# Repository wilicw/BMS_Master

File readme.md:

# BMS Master board PCB
NCKU Formula racing 2025
BMS Master using TI's BQ79600-Q1 as communication module and STM32F103C8T6 as MCU

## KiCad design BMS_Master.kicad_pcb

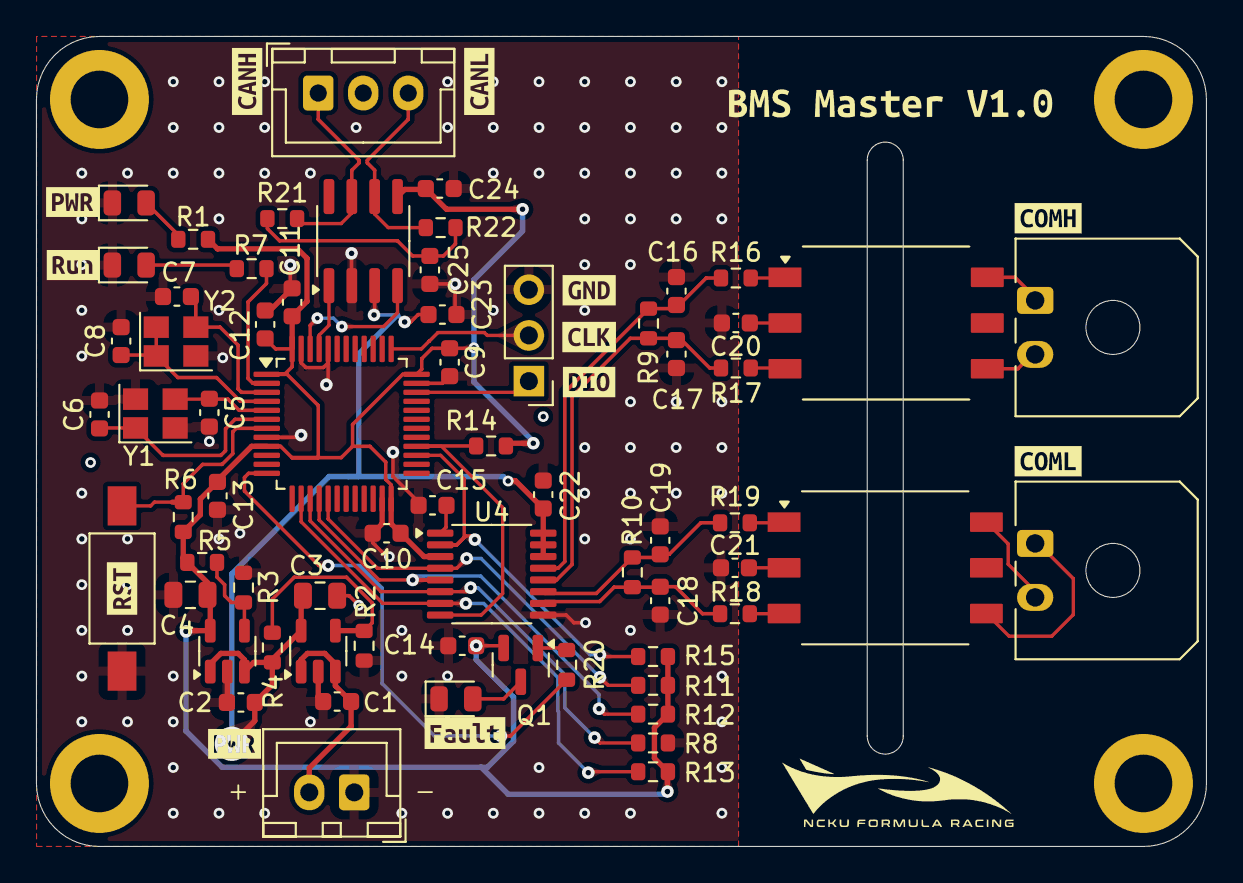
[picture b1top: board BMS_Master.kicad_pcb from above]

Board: 2 copper layers, 65.0 x 45.0 mm, 83 parts (0 on the bottom side), 45 nets.

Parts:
C1, C2, C25: 1u; C_0603_1608Metric
C3, C4: 10u; C_0805_2012Metric
C5, C6, C7, C8: 20p; C_0603_1608Metric
C9, C10, C11, C12, C13, C23, C24: 100n; C_0603_1608Metric
C14, C15, C22: 220n; C_0603_1608Metric
C16, C17, C18, C19: 220p; C_0603_1608Metric
C20, C21: 100p; C_0603_1608Metric
D1: PWR_Yellow; LED_0805_2012Metric
D2: RUN_GREEN; LED_0805_2012Metric
D3: FAULT_RED; LED_0805_2012Metric
H1, H2, H3, H4: MountingHole_Pad; MountingHole_3.2mm_M3_ISO14580_Pad
J1: PWR; JST_XH_B2B-XH-A_1x02_P2.50mm_Vertical
J2: PROG; PinHeader_1x03_P2.54mm_Vertical
J3: BMS_M_OUT; Molex_Micro-Fit_3.0_43650-0200_1x02_P3.00mm_Horizontal
J4: BMS_M_IN; Molex_Micro-Fit_3.0_43650-0200_1x02_P3.00mm_Horizontal
J5: CAN; JST_XH_B3B-XH-A_1x03_P2.50mm_Vertical
Q1: BC807; SOT-23
R1, R7, R9, R10: 1k; R_0603_1608Metric
R2, R3: 100k; R_0603_1608Metric
R4: 301k; R_0603_1608Metric
R5: 165k; R_0603_1608Metric
R6: 10k; R_0603_1608Metric
R8, R11, R12, R13, R20: 10K; R_0603_1608Metric
R14, R15: 100K; R_0603_1608Metric
R16, R17, R18, R19: 49R; R_0603_1608Metric
R21, R22: 60R; R_0603_1608Metric
SW1: SW_SPST; SW_SPST_FSMSM
TR1, TR2: Wuerth_750319696; Transformer_Wuerth_750315371
U1, U2: AP2204K-ADJ; SOT-23-5
U3: STM32F103C8Tx; LQFP-48_7x7mm_P0.5mm
U4: BQ79600-Q1; TSSOP-16_4.4x5mm_P0.65mm
U5: SN65HVD256D; SOIC-8_3.9x4.9mm_P1.27mm
Y1: 8M; Crystal_SMD_SeikoEpson_FA238-4Pin_3.2x2.5mm
Y2: 32.768k; Crystal_SMD_SeikoEpson_FA238-4Pin_3.2x2.5mm
kibuzzard-679F52AD: G***; kibuzzard-679F52AD
kibuzzard-679F52BD: G***; kibuzzard-679F52BD
kibuzzard-679F55A0: G***; kibuzzard-679F55A0
kibuzzard-679F55DD: G***; kibuzzard-679F55DD
kibuzzard-679F55F7: G***; kibuzzard-679F55F7
kibuzzard-679F56A0: G***; kibuzzard-679F56A0
kibuzzard-679F56A8: G***; kibuzzard-679F56A8
kibuzzard-679F550D: G***; kibuzzard-679F550D
kibuzzard-679F551A: G***; kibuzzard-679F551A
kibuzzard-679F561D: G***; kibuzzard-679F561D
kibuzzard-679F5580: G***; kibuzzard-679F5580
kibuzzard-679F5696: G***; kibuzzard-679F5696
kibuzzard-6797C095: G***; kibuzzard-6797C095

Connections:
+5V: C2.2, C3.2, C22.1, C23.2, R4.2, U1.5 (VOUT), U2.1 (VIN), U2.3 (EN), U4.14 (CVDD), U4.15 (BAT), U4.16 (INH), U5.3 (VCC)
+24V: C1.2, J1.2, U1.1 (VIN), U1.3 (EN)
/LSE_IN: C7.1, U3.3 (PC14), Y2.3
/LSE_OUT: C8.1, U3.4 (PC15), Y2.1, Y2.4
BMS_FAULT: R20.2, U3.12 (PA2)
CAN_N: J5.3, R22.1, U5.6 (CANL)
CAN_P: J5.1, R21.2, U5.7 (CANH)
CAN_RX: U3.45 (PB8), U5.1 (TXD)
CAN_TX: U3.46 (PB9), U5.4 (RXD)
COMHN: C17.1, R9.2, R17.1, U4.12 (COMHN)
COMHP: C16.1, R9.1, R16.1, U4.13 (COMHP)
COMLN: C19.1, R10.2, R19.1, U4.11 (COMLN)
COMLP: C18.1, R10.1, R18.1, U4.10 (COMLP)
GND: C1.1, C2.1, C3.1, C4.1, C5.2, C6.2, C7.2, C8.2, C9.2, C10.2, C11.2, C12.2, C13.2, C14.1, C15.1, C16.2, C17.2, C18.2, C19.2, C20.2, C21.2, C22.2, C23.1, C24.1, C25.1, D1.1 (K), D2.1 (K), D3.1 (K), J1.1, J2.3, R2.1, R3.1, R8.2, SW1.1 (A), U1.2 (GND), U2.2 (GND), U3.8 (VSSA), U3.23 (VSS), U3.35 (VSS), U3.44 (BOOT0), U3.47 (VSS), U4.9 (GND), U5.2 (GND), Y1.2, Y1.4, Y2.2
MISO: R12.2, U3.16 (PA6), U4.5 (MISO/TX)
MOSI: R11.2, U3.17 (PA7), U4.4 (MOSI/RX)
NFAULT: R15.2, U3.27 (PB14), U4.2 (NFAULT)
unnamed: C20.1, TR1.2
unnamed: C21.1, TR2.2
unnamed: C25.2, R21.1, R22.2
unnamed: D1.2 (A), R1.1
unnamed: D2.2 (A), R7.1
unnamed: D3.2 (A), Q1.3 (C)
unnamed: J3.1, TR1.6
unnamed: J3.2, TR1.4
unnamed: J4.1, TR2.4
unnamed: J4.2, TR2.6
unnamed: Q1.1 (B), R20.1
unnamed: R16.2, TR1.1
unnamed: R17.2, TR1.3
unnamed: R18.2, TR2.3
unnamed: R19.2, TR2.1
unnamed: R6.2, SW1.2 (B), U3.7 (NRST)
unnamed: R2.2, R4.1, U1.4 (ADJ)
unnamed: R3.2, R5.1, U2.4 (ADJ)
unnamed: C5.1, U3.5 (PD0), Y1.3
unnamed: C6.1, U3.6 (PD1), Y1.1
unnamed: C15.2, U4.1 (DVDD)
RUN_LED: R7.2, U3.2 (PC13)
SCLK: R8.1, U3.15 (PA5), U4.6 (SCLK)
SPI_RDY: R14.2, U3.28 (PB15), U4.8 (nUART/SPI(SPI_RDY))
SWCLK: J2.2, U3.37 (PA14)
SWDIO: J2.1, U3.34 (PA13)
VIO: C4.2, C9.1, C10.1, C11.1, C12.1, C13.1, C14.2, C24.2, Q1.2 (E), R1.2, R5.2, R6.1, R11.1, R12.1, R13.1, R14.1, R15.1, U2.5 (VOUT), U3.1 (VBAT), U3.9 (VDDA), U3.24 (VDD), U3.36 (VDD), U3.48 (VDD), U4.3 (VIO), U5.5 (VRXD)
nCS: R13.2, U3.14 (PA4), U4.7 (nCS)

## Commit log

2025-01-24 First commit, initiate new BMS master board project
2025-01-24 Add can bus transeiver and Readme.md
2025-01-24 Finish schematic (probably)
2025-01-25 Finish schematic (For real), for basic requirements
2025-01-26 Initiate PCB layout and make some arrangement in Schematic
2025-01-27 Finish PCB layout Ver 1.0
2025-01-28 Adjust silk print word position
2025-01-28 Add via holes and teardrops
2025-02-02 Fix layout problems
2025-02-02 Add size label in user layer and adjust sheet size
2025-02-03 Fix edge cuts and DRC
2025-02-03 Add output path and export step
2025-02-05 Fix crystal pinout connection
2025-02-11 Add current sensor ADC port
2025-02-11 Finish layout ver 1, already abandoned
